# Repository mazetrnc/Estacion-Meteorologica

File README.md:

[Monitoreo de Estación Meteorológica en ThingSpeak](https://thingspeak.mathworks.com/channels/3108150) 

<h3>Funcionamiento de la Estación Meteorológica</h3>

La estación meteorológica desarrollada utiliza una **ESP32 como unidad central de procesamiento**, encargada de adquirir, procesar y transmitir los datos obtenidos por diversos sensores ambientales. El sistema integra varios módulos conectados principalmente mediante el protocolo **I2C**, así como comunicación **UART/RS485**, lo que permite medir múltiples variables meteorológicas y ambientales en tiempo real.

En primer lugar, el sensor **BME280** mide tres variables fundamentales del clima: **temperatura, humedad relativa y presión atmosférica**. A partir de la presión también se calcula la **altitud aproximada** utilizando una presión de referencia al nivel del mar. Estos datos son obtenidos a través del bus I2C y se almacenan en variables para su posterior procesamiento.

La calidad del aire se monitorea mediante el sensor **SGP30**, que proporciona estimaciones de **CO₂ equivalente (eCO₂)** y **compuestos orgánicos volátiles totales (TVOC)**. Para mejorar la precisión de las mediciones, el código calcula la **humedad absoluta** a partir de los datos del BME280 y la envía al SGP30 como parámetro de compensación ambiental.

La **radiación ultravioleta** se mide con el sensor **LTR390**, también conectado por I2C, el cual proporciona un valor de radiación UV que puede relacionarse con el **índice UV utilizado por organismos de salud**.

Para medir la **precipitación**, se utiliza un **sensor de lluvia con cubeta basculante**, que contabiliza los pulsos generados por cada basculación causada por la acumulación de agua. El código convierte estos pulsos en **milímetros de lluvia acumulada**, permitiendo conocer la precipitación en un periodo determinado.

La **velocidad del viento** se obtiene mediante un **anemómetro con salida RS485**, que transmite los datos usando el protocolo **Modbus RTU**. Debido a que la ESP32 trabaja con niveles TTL, se emplea un **módulo conversor MAX485** para adaptar la señal RS485 a comunicación serial. El código envía una solicitud Modbus al anemómetro, recibe la respuesta, verifica su integridad mediante **CRC16**, y finalmente convierte el valor recibido en **metros por segundo (m/s)**.

Una vez que la ESP32 realiza la lectura de todos los sensores integrados (aproximadamente cada **5 segundos**), procesa la información y la expone mediante una arquitectura de red dual que combina monitoreo local e IoT en la nube simultáneamente:

1. **Servidor Web Local en Tiempo Real (Modo AP):** La ESP32 crea un punto de acceso Wi-Fi propio (`SSID: EstacionMeteo`) donde aloja un **servidor web asíncrono (`ESPAsyncWebServer`)** en la IP `192.168.4.1`. La interfaz web (almacenada en `PROGMEM` / `pagina_web.h`) consulta automáticamente el endpoint `/datos` mediante peticiones `XMLHttpRequest` en segundo plano **cada 10 segundos**. Esto actualiza los indicadores, alertas y gráficos locales de forma instantánea sin requerir recargas de página ni depender de una conexión a Internet.

2. **Publicación Remota en la Nube (Modo STA - ThingSpeak):** De forma paralela y utilizando la misma interfaz de red (`WIFI_AP_STA`), la ESP32 se conecta como cliente a un router local con salida a Internet. **Cada 5 minutos (`POST_INTERVAL_MS = 300000`)**, el microcontrolador realiza una **petición HTTP GET** al servidor de **ThingSpeak** (`api.thingspeak.com`), mapeando las lecturas a los campos del canal:

* **Field 1:** Temperatura (°C)

* **Field 2:** Humedad (%)

* **Field 3:** Presión (hPa)

* **Field 4:** Velocidad del viento (m/s)

* **Field 5:** eCO₂ (ppm)

* **Field 6:** TVOC (ppb)

* **Field 7:** Precipitación / Tasa (mm/h)

* **Field 8:** Índice UV (OMS)

Ambos modos funcionan simultáneamente y de forma totalmente independiente: si la conexión Wi-Fi a Internet falla o no está disponible, el envío a ThingSpeak se omite temporalmente sin afectar la operación del servidor web local, el cual sigue sirviendo los datos en tiempo real de forma ininterrumpida.

En conjunto, esta estación meteorológica integra sensores ambientales de precisión, protocolos de comunicación industrial y de bus (I2C y RS485/Modbus RTU), servidor web embebido y conectividad IoT híbrida para crear un sistema robusto capaz de **monitorear condiciones climáticas en tiempo real de forma local y, al mismo tiempo, publicar los resultados en una plataforma en la nube para su almacenamiento histórico y análisis remoto**.

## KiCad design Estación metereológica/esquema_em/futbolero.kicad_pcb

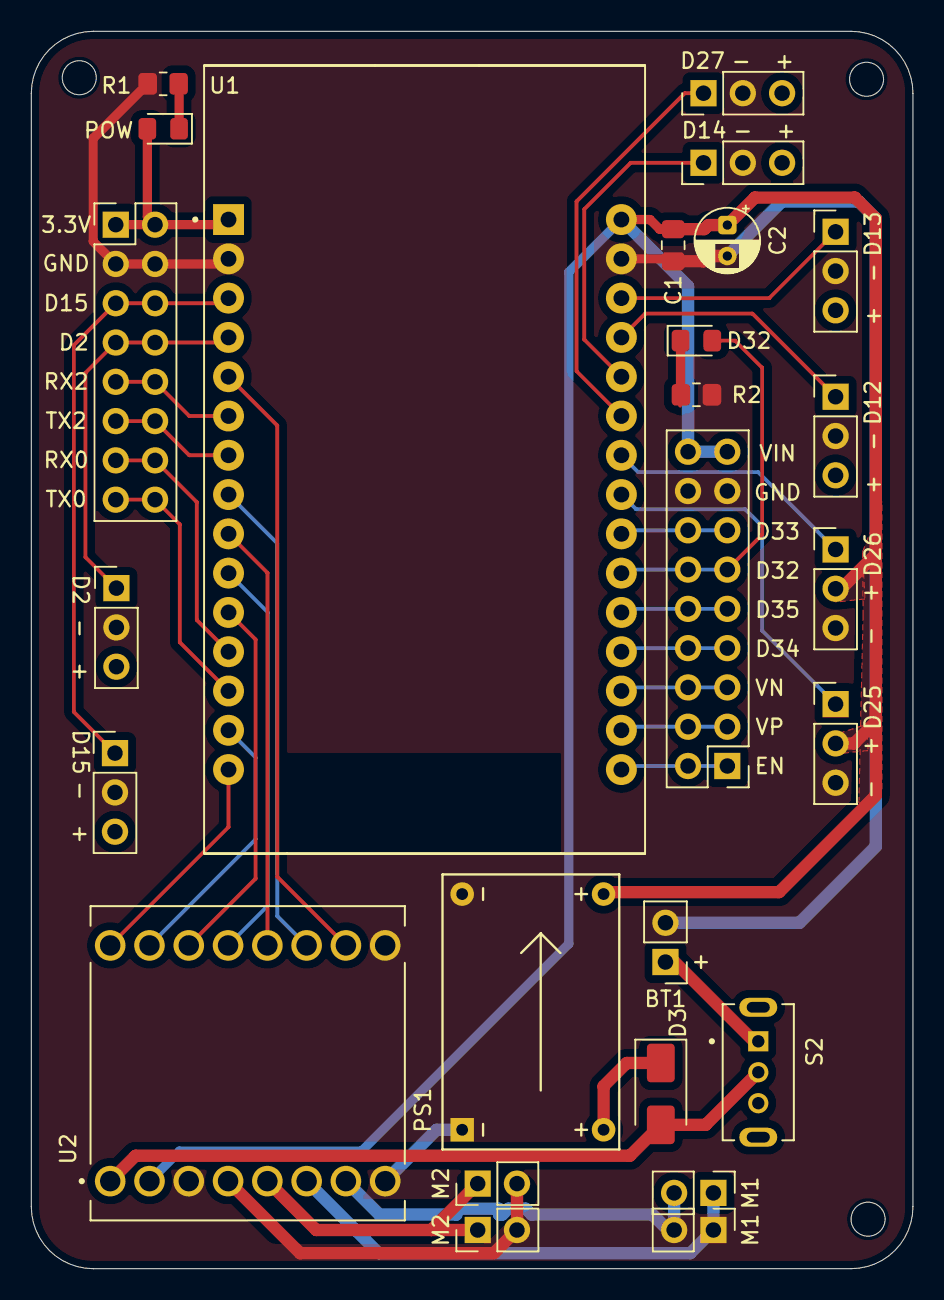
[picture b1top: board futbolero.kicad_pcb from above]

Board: 2 copper layers, 57.0 x 80.0 mm, 26 parts (0 on the bottom side), 38 nets.

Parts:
BT1: Battery; PinHeader_1x02_P2.54mm_Vertical
C1: 0.1u; C_0805_2012Metric_Pad1.18x1.45mm_HandSolder
C2: 10u; CP_Radial_D4.0mm_P2.00mm
D3: SS34; D_SMA
D32: LED; LED_0805_2012Metric_Pad1.15x1.40mm_HandSolder
J1: Conn_02x08_Odd_Even; PinHeader_2x08_P2.54mm_Vertical
J2: Conn_02x09_Odd_Even; PinHeader_2x09_P2.54mm_Vertical
J3, J4, J5, J6, J7, J8, J9, J10: Conn_01x03; PinHeader_1x03_P2.54mm_Vertical
M1, M1#2, M2, M2#2: Motor_DC; PinHeader_1x02_P2.54mm_Vertical
POW: LED; LED_0805_2012Metric_Pad1.15x1.40mm_HandSolder
PS1: Mini-360 Buck Converter; Mini360_Module
R1, R2: 22; R_0805_2012Metric_Pad1.20x1.40mm_HandSolder
S2: SS12D07VG4; SW_SS12D07VG4
U1: ESP32-DEVKIT-V1; MODULE_ESP32_DEVKIT_V1
U2: TB6612FNG; MODULE_TB6612FNG

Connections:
3.3V: J1.1, J1.2, J3.3, J4.3, J5.3, J8.3, J9.3, J10.3, POW.2 (A), U1.1 (3V3)
+7.5V: BT1.1 (+), S2.1
D2: J1.7, J1.8, J4.1, U1.4 (D2)
D4: U1.5 (D4), U2.10 (PWMB)
D5: U1.8 (D5), U2.11 (BI2)
D12: J5.1, U1.27 (D12)
D13: J8.1, U1.28 (D13)
D14: J10.1, U1.26 (D14)
D15: J1.5, J1.6, J3.1, U1.3 (D15)
D18: U1.9 (D18), U2.12 (BI1)
D19: U1.10 (D19), U2.13 (STBY)
D21: U1.11 (D21), U2.14 (AI1)
D22: U1.14 (D22), U2.15 (AI2)
D23: U1.15 (D23), U2.16 (PWMA)
D25: J7.1, U1.23 (D25)
D26: J6.1, U1.24 (D26)
D27: J9.1, U1.25 (D27)
D32: D32.2 (A), J2.11, J2.12, U1.21 (D32)
D33: J2.13, J2.14, U1.22 (D33)
D34: J2.7, J2.8, U1.19 (D34)
D35: J2.9, J2.10, U1.20 (D35)
EN: J2.1, J2.2, U1.16 (EN)
GND: BT1.2 (-), C1.1, C2.2, J1.3, J1.4, J2.15, J2.16, J3.2, J4.2, J5.2, J6.3, J7.3, J8.2, J9.2, J10.2, PS1.2 (-Vin), PS1.4 (-Vout), R1.2, R2.2, U1.2 (GND), U1.29 (GND), U2.3 (GND), U2.8 (GND), U2.9 (GND)
unnamed: POW.1 (K), R1.1
unnamed: D32.1 (K), R2.1
unnamed: D3.1 (K), PS1.1 (+Vin)
unnamed: M1.1 (+), M1#2.1 (+), U2.6 (B02)
unnamed: M1.2 (-), M1#2.2 (-), U2.7 (B01)
unnamed: M2.1 (+), M2#2.1 (+), U2.5 (A02)
unnamed: M2.2 (-), M2#2.2 (-), U2.4 (A01)
RX0: J1.13, J1.14, U1.12 (RX0)
RX2: J1.9, J1.10, U1.6 (RX2)
TX0: J1.15, J1.16, U1.13 (TX0)
TX2: J1.11, J1.12, U1.7 (TX2)
VIN: D3.2 (A), S2.2, U2.1 (VM)
VN: J2.5, J2.6, U1.18 (VN)
VOUT: C1.2, C2.1, J2.17, J2.18, J6.2, J7.2, PS1.3 (+Vout), U1.30 (VIN), U2.2 (VCC)
VP: J2.3, J2.4, U1.17 (VP)

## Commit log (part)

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2026-03-12 Add link to ThingSpeak weather station monitoring
2026-03-12 Enhance README with weather station functionality details
    Added detailed description of the weather station functionality, including sensor integration and data transmission to ThingSpeak.
2026-03-12 Enhance README with weather station functionality details
    Added detailed explanation of the weather station's functionality, including sensor descriptions and data transmission methods.
